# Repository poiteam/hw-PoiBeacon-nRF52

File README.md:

# hw-PoiBeacon-nRF52
This repo includes circuit design of nRF52 Beacon families.

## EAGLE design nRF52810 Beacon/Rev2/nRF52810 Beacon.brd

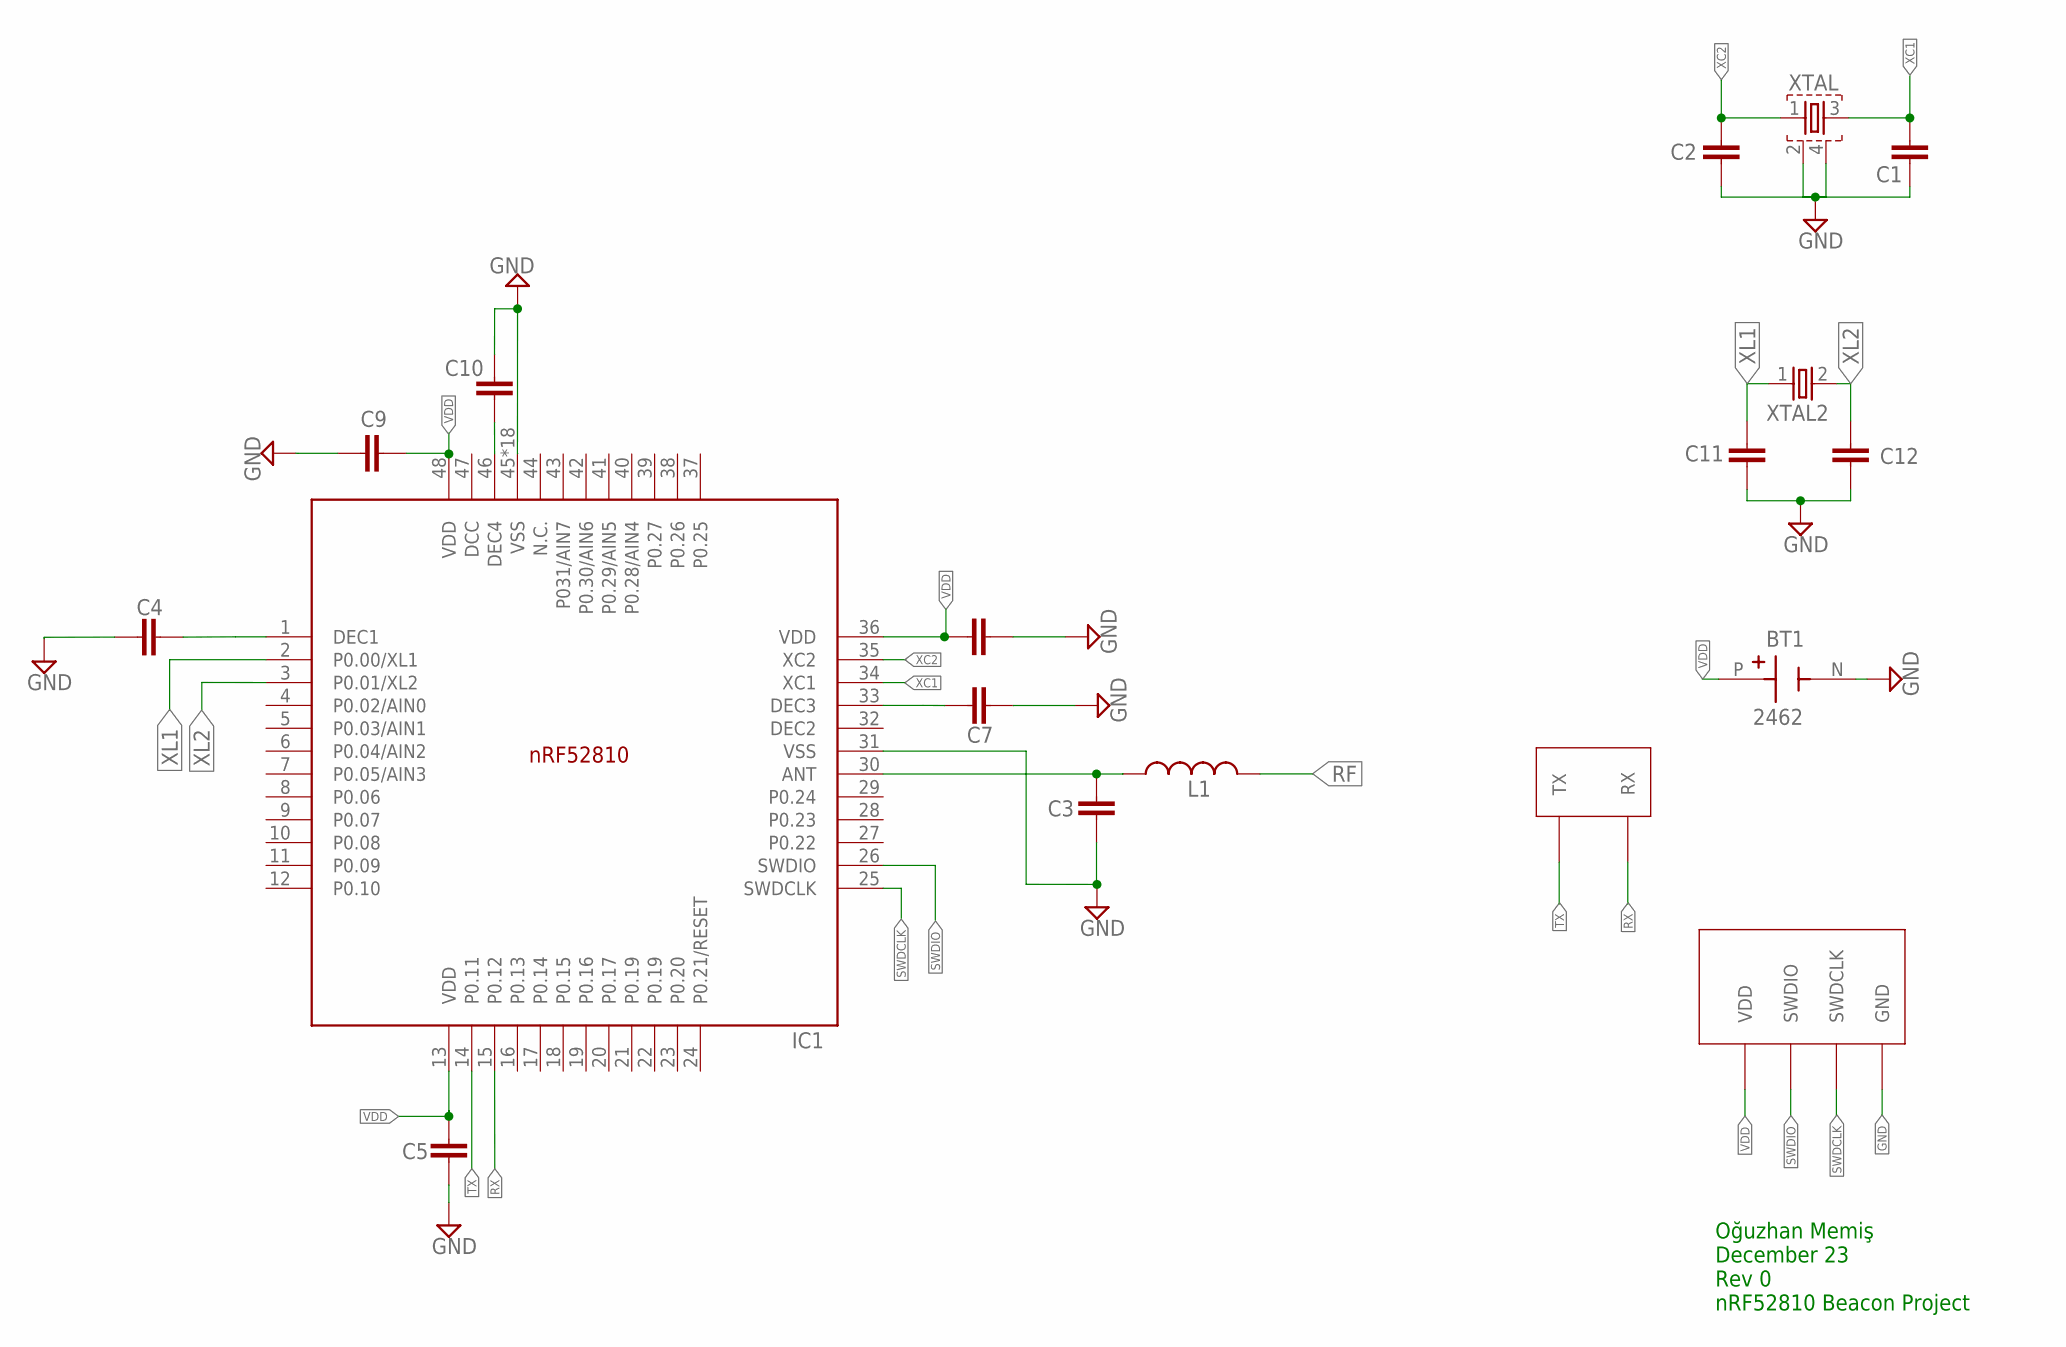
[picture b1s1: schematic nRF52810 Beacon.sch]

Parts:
BT1: 2462; BAT_2462
C1, C2, C11, C12: 12pF; RESC0402_N
C3: 0.8pF; RESC0402_N
C4, C5, C8: 100nF; RESC0402_N
C7: 100pF; RESC0402_N
C9: 4.7uF; RESC0603_N
C10: 1uF; RESC0603_N
IC1: NRF52810_QF48; QFN40P600X600X90-48_N
L1: 3.9nF; RESC0402_N
U$1: SWD
U$2: UART
XTAL: 32MHz SMD2016; BT-XTAL_2016_N
XTAL2: 32KHz; XTAL_3215_N

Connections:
GND: BT1.N (NEG), C1.1, C2.1, C3.2, C4.1, C5.2, C7.2, C8.2, C9.1, C10.2, C11.1, C12.1, IC1.31 (VSS), IC1.45 (VSS), IC1.PAD (VSS), IC1.PAD@VIA01 (VSS), IC1.PAD@VIA02 (VSS), IC1.PAD@VIA03 (VSS), IC1.PAD@VIA04 (VSS), IC1.PAD@VIA05 (VSS), IC1.PAD@VIA06 (VSS), IC1.PAD@VIA07 (VSS), IC1.PAD@VIA08 (VSS), IC1.PAD@VIA09 (VSS), IC1.PAD@VIA10 (VSS), IC1.PAD@VIA11 (VSS), IC1.PAD@VIA12 (VSS), IC1.PAD@VIA13 (VSS), IC1.PAD@VIA14 (VSS), IC1.PAD@VIA15 (VSS), IC1.PAD@VIA16 (VSS), U$1.GND, XTAL.2, XTAL.4
unnamed: C10.1, IC1.46 (DEC4)
unnamed: C7.1, IC1.33 (DEC3)
unnamed: C4.2, IC1.1 (DEC1)
unnamed: C3.1, IC1.30 (ANT), L1.1
RF: L1.2
RX: IC1.15 (P0.12), U$2.RX
SWDCLK: IC1.25 (SWDCLK), U$1.SWDCLK
SWDIO: IC1.26 (SWDIO), U$1.SWDIO
TX: IC1.14 (P0.11), U$2.TX
VDD: BT1.P (POS), C5.1, C8.1, C9.2, IC1.13 (VDD), IC1.36 (VDD), IC1.48 (VDD), U$1.VDD
XC1: C1.2, IC1.34 (XC1), XTAL.3
XC2: C2.2, IC1.35 (XC2), XTAL.1
XL1: C11.2, IC1.2 (P0.00/XL1), XTAL2.1
XL2: C12.2, IC1.3 (P0.01/XL2), XTAL2.2

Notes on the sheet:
Oğuzhan Memiş December 23 Rev 0 nRF52810 Beacon Project

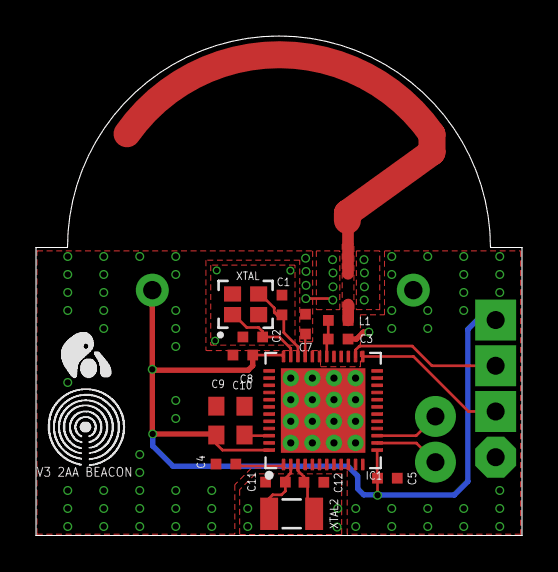
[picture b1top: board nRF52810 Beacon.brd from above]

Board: 2 copper layers, 27.0 x 27.8 mm, 20 parts (1 on the bottom side), 14 nets.

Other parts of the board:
U$3: POILOGO
U$4: IBEACON

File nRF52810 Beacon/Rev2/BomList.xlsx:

Comment | Designator | Footprint
12pF | C1,C2,C11,C12 | 402
0.8pF | C3 | 402
100nF | C4,C5,C8 | 402
100pF | C7 | 402
4.7uF | C9 | 603
1uF | C10 | 603
nRF52810_QF48 | IC1 | QFN40P600X600X90-48_N
3.9nF | L1 | 402
32MHZ | XTAL | BT-XTAL_2016_N
32KHZ | XTAL2 | XTAL_3215_N
BATTERY HOLDER | BT1 | BT_2462

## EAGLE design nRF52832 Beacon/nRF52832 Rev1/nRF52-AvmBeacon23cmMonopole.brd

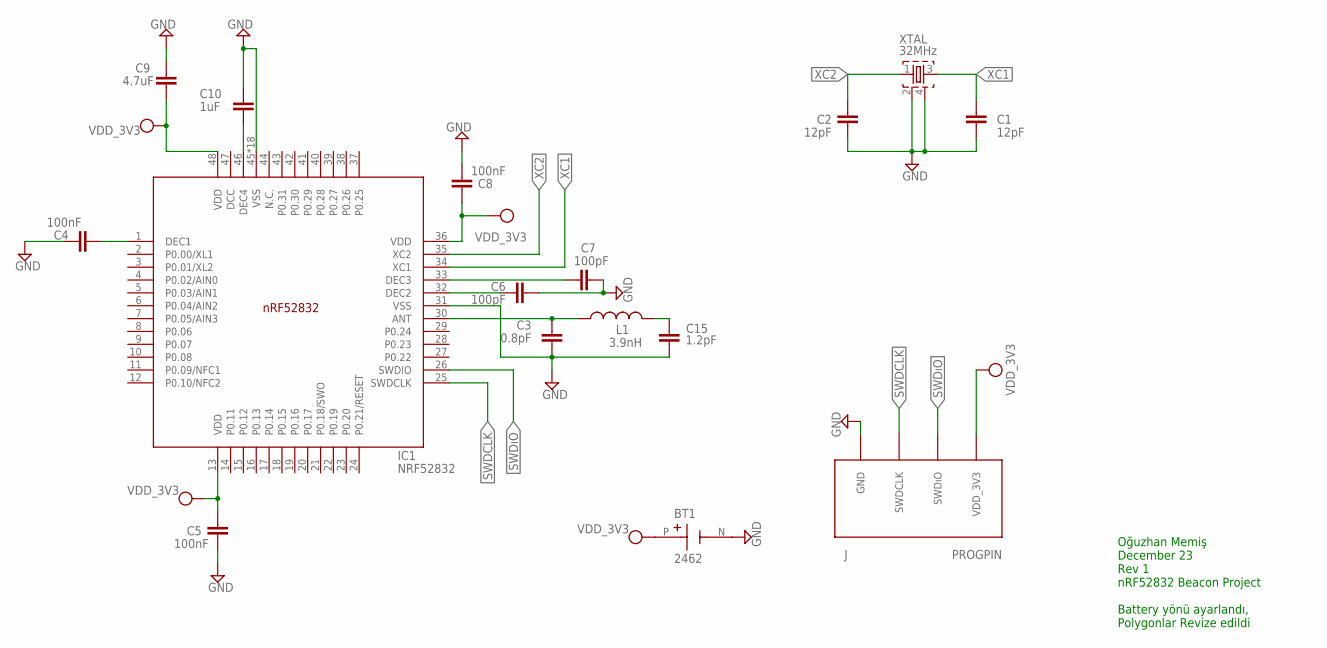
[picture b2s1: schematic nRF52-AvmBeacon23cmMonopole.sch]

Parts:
BT1: 2462; BAT_2462
C1, C2: 12pF; RESC0402_N
C3: 0.8pF; RESC0402_N
C4, C5, C8: 100nF; RESC0402_N
C6, C7: 100pF; RESC0402_N
C9: 4.7uF; RESC0603_N
C10: 1uF; RESC0603_N
C15: 1.2pF; RESC0402_N
IC1: NRF52832; QFN40P600X600X90-48_N
L1: 3.9nH; RESC0402_N
U$1: PROGPIN4*2.54; PROGPIN
XTAL: 32MHz; BT-XTAL_2016_N

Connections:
GND: BT1.N (NEG), C1.2, C2.2, C3.1, C4.1, C5.2, C6.2, C7.2, C8.2, C9.1, C10.1, C15.2, IC1.31 (VSS), IC1.45 (VSS), IC1.PAD (VSS), IC1.PAD@VIA01 (VSS), IC1.PAD@VIA02 (VSS), IC1.PAD@VIA03 (VSS), IC1.PAD@VIA04 (VSS), IC1.PAD@VIA05 (VSS), IC1.PAD@VIA06 (VSS), IC1.PAD@VIA07 (VSS), IC1.PAD@VIA08 (VSS), IC1.PAD@VIA09 (VSS), IC1.PAD@VIA10 (VSS), IC1.PAD@VIA11 (VSS), IC1.PAD@VIA12 (VSS), IC1.PAD@VIA13 (VSS), IC1.PAD@VIA14 (VSS), IC1.PAD@VIA15 (VSS), IC1.PAD@VIA16 (VSS), U$1.GND, XTAL.2, XTAL.4
unnamed: C4.2, IC1.1 (DEC1)
unnamed: C3.2, IC1.30 (ANT), L1.1
unnamed: C6.1, IC1.32 (DEC2)
unnamed: C7.1, IC1.33 (DEC3)
unnamed: C10.2, IC1.46 (DEC4)
SWDCLK: IC1.25 (SWDCLK), U$1.SWDCLK
SWDıO: IC1.26 (SWDIO), U$1.SWDIO (SWDıO)
TL: C15.1, L1.2
VDD: BT1.P (POS), C5.1, C8.1, C9.2, IC1.13 (VDD), IC1.36 (VDD), IC1.48 (VDD), U$1.VDD_3V3
XC1: C1.1, IC1.34 (XC1), XTAL.3
XC2: C2.1, IC1.35 (XC2), XTAL.1

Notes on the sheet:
Oğuzhan Memiş December 23 Rev 1 nRF52832 Beacon Project Battery yönü ayarlandı, Polygonlar Revize edildi

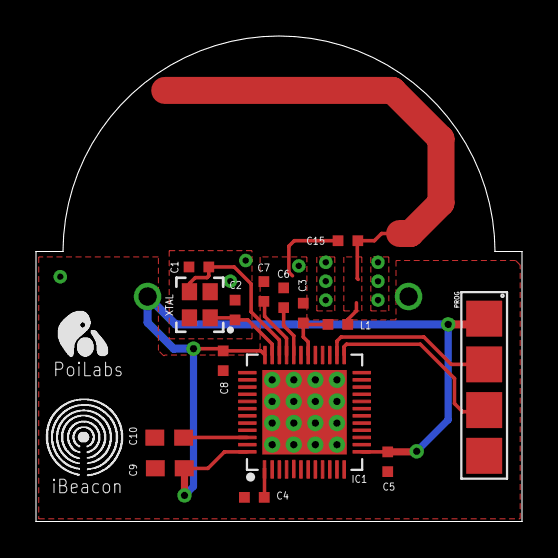
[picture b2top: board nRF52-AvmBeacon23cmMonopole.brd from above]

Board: 2 copper layers, 27.0 x 27.0 mm, 18 parts (1 on the bottom side), 12 nets.

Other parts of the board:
U$2: IBEACON
U$3: POILOGO

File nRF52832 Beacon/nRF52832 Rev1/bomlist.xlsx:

Comment | Designator | Footprint
0.8pF | C3 | RESC0402_N
1.2pF | C15 | RESC0402_N
1uF | C10 | RESC0603_N
3.9nF | L1 | RESC0402_N
4.7uF | C9 | RESC0603_N
NRF52832 | IC1 | QFN48
100pF | C6,C7 | RESC0402_N
12pF | C1, C2 | RESC0402_N
100nF | C4, C5, C8 | RESC0402_N
32MHz | XTAL | BT-XTAL_2916

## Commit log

2024-02-01 nRF52832 ve nRF52810 Çizimleri repoya eklendi
2024-02-11 nrf52810 için revizyonlar yapıldı
2024-02-12 nrf52 revizeler
2024-02-13 devre revizeleri
2024-02-14 sipariş verildi ar-ge'ye devam
2024-03-13 R3 eklendi dcdc iptal ldo devam 32khz devam
